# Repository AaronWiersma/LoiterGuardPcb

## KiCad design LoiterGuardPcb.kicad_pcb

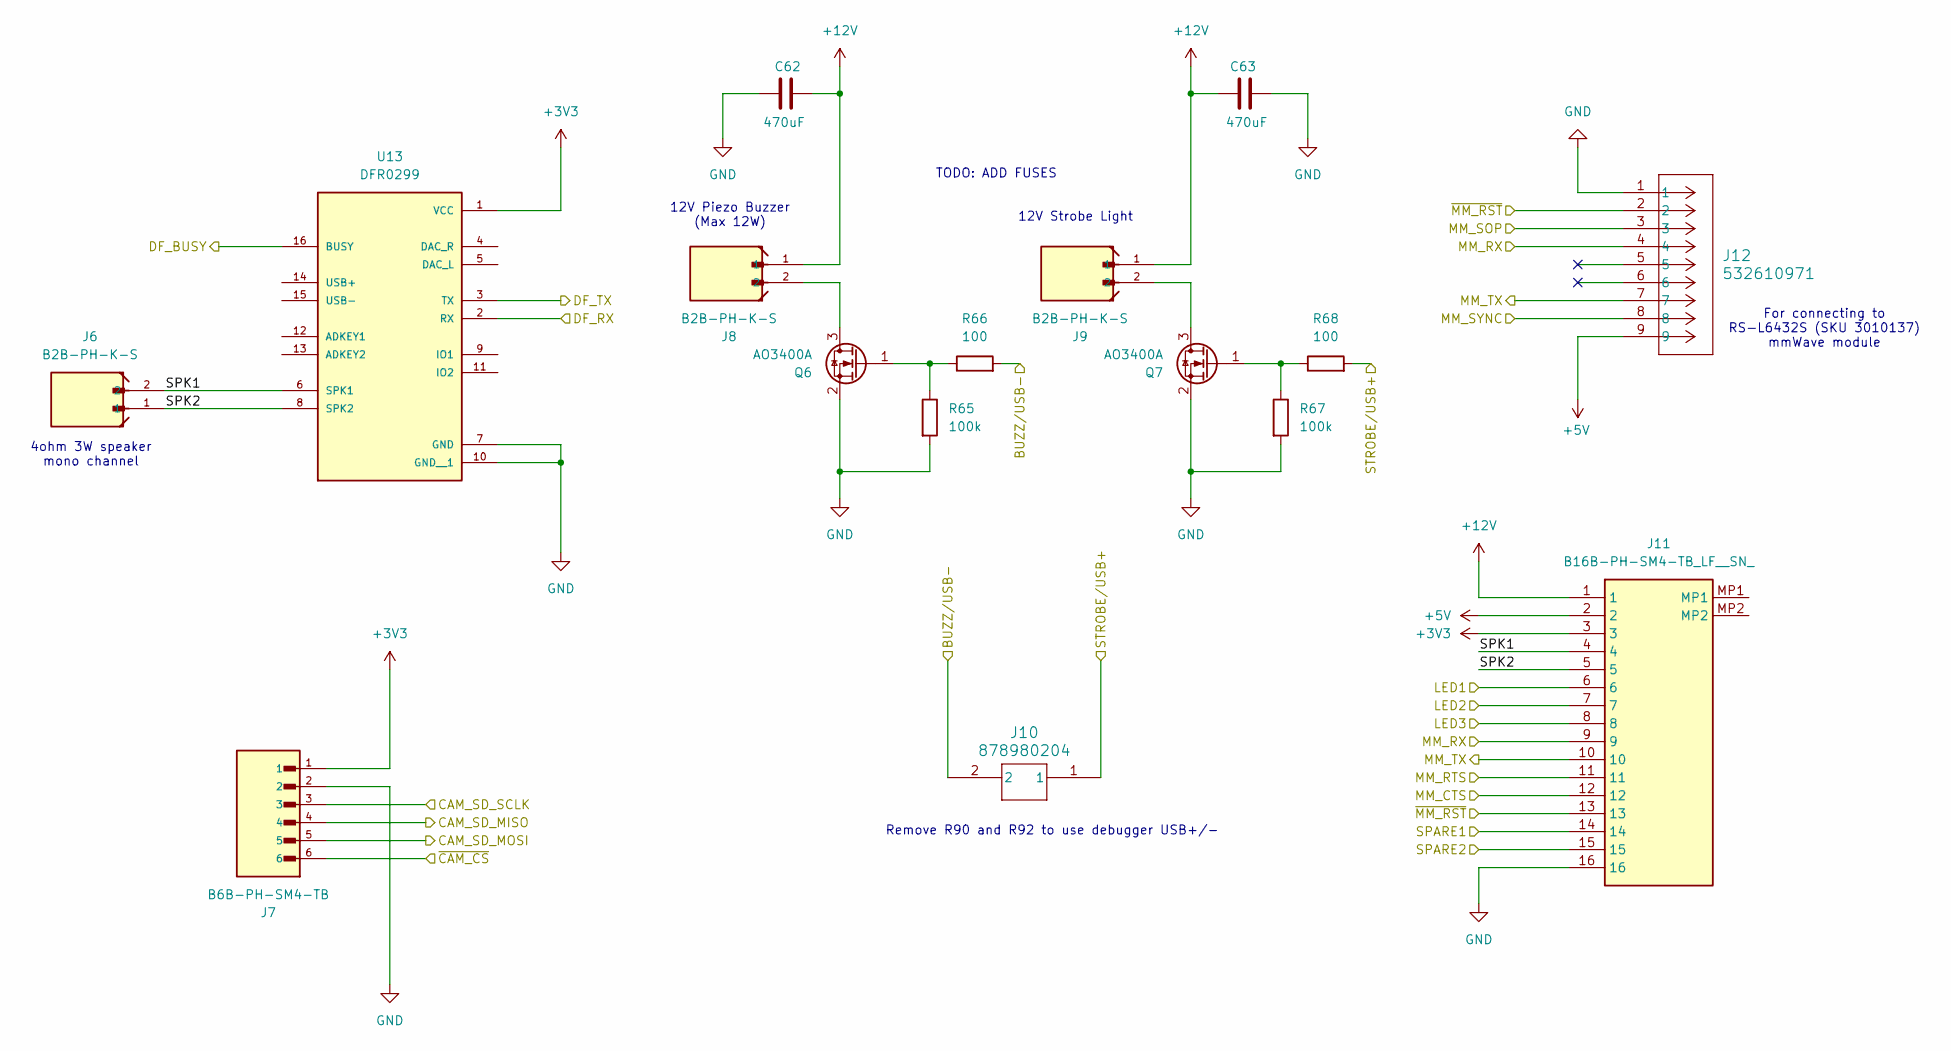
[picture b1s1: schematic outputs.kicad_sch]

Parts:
C62, C63: 470uF; CP_Radial_D10.0mm_P5.00mm
J6, J8, J9: B2B-PH-K-S; JST_B2B-PH-K-S
J7: B6B-PH-SM4-TB; JST_B6B-PH-SM4-TB; PARTREV N/A
J10: 878980204; 87898-0204_MOL
J11: B16B-PH-SM4-TB_LF__SN_; B16BPHSM4TBLFSN; Manufacturer_Part_Number B16B-PH-SM4-TB(LF)(SN); Mouser Part Number 306-B16BPHSM4TBLFSN
J12: 532610971; CONN_532610001-SD_09_MOL
Q6, Q7: AO3400A; SOT-23
R65, R67: 100k; R_0603_1608Metric
R66, R68: 100; R_0603_1608Metric
U13: DFR0299; MODULE_DFR0299

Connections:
+3V3: J7.1, J11.3, U13.1 (VCC); also elsewhere on the board
+5V: J11.2, J12.9; also elsewhere on the board
+12V: C62.2, C63.2, J8.1, J9.1, J11.1; also elsewhere on the board
/Expander/CAM_SD_MISO: J7.4; also elsewhere on the board
/Expander/CAM_SD_MOSI: J7.5; also elsewhere on the board
/Expander/CAM_SD_SCLK: J7.3; also elsewhere on the board
/Expander/DF_BUSY: U13.16 (BUSY); also elsewhere on the board
/Expander/MM_SOP: J12.3; also elsewhere on the board
/Expander/MM_SYNC: J12.8; also elsewhere on the board
/Expander/SPARE1: J11.15; also elsewhere on the board
/Expander/SPARE2: J11.14; also elsewhere on the board
/Expander/~MM_RST: J11.13, J12.2; also elsewhere on the board
/MCU/BUZZ/USB-: J10.2, R66.2; also elsewhere on the board
/MCU/DF_RX: U13.2 (RX); also elsewhere on the board
/MCU/DF_TX: U13.3 (TX); also elsewhere on the board
/MCU/LED1: J11.6; also elsewhere on the board
/MCU/LED2: J11.7; also elsewhere on the board
/MCU/LED3: J11.8; also elsewhere on the board
/MCU/MM_CTS: J11.12; also elsewhere on the board
/MCU/MM_RTS: J11.11; also elsewhere on the board
/MCU/MM_RX: J11.9, J12.4; also elsewhere on the board
/MCU/MM_TX: J11.10, J12.7; also elsewhere on the board
/MCU/STROBE/USB+: J10.1, R68.2; also elsewhere on the board
/MCU/~CAM_CS: J7.6; also elsewhere on the board
/Outputs/SPK1: J6.2, J11.4, U13.6 (SPK1)
/Outputs/SPK2: J6.1, J11.5, U13.8 (SPK2)
GND: C62.1, C63.1, J7.2, J11.16, J12.1, Q6.2 (S), Q7.2 (S), R65.2, R67.2, U13.7 (GND), U13.10 (GND__1); also elsewhere on the board
unnamed: J8.2, Q6.3 (D)
unnamed: Q6.1 (G), R65.1, R66.1
unnamed: J9.2, Q7.3 (D)
unnamed: Q7.1 (G), R67.1, R68.1

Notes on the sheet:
TODO: ADD FUSES
12V Strobe Light
Remove R90 and R92 to use debugger USB+/-
12V Piezo Buzzer (Max 12W)
4ohm 3W speaker mono channel
For connecting to RS-L6432S (SKU 3010137) mmWave module

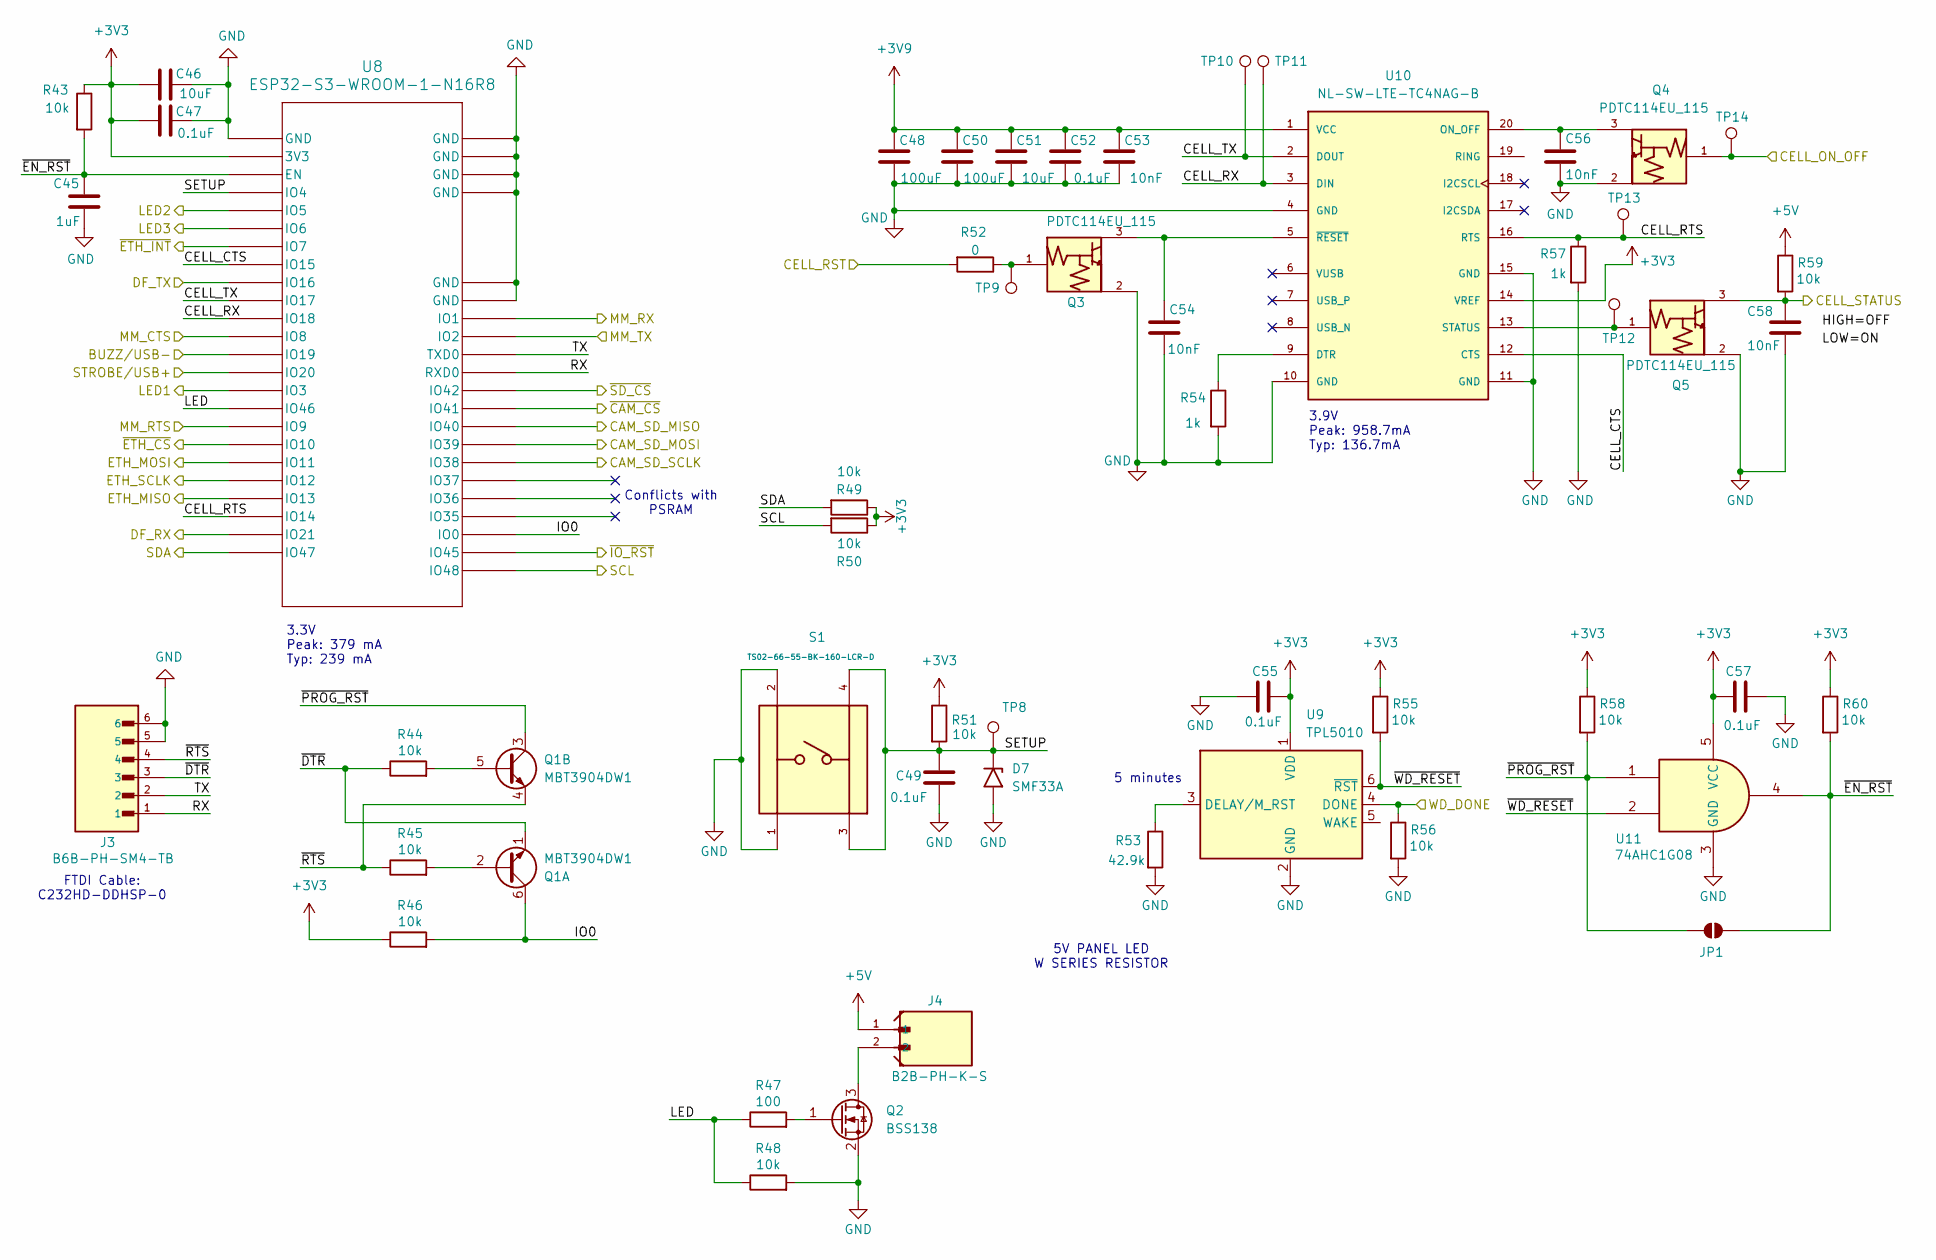
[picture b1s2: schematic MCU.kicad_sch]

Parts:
C45: 1uF; C_0603_1608Metric
C46, C51: 10uF; C_0805_2012Metric
C47, C49, C52, C55, C57: 0.1uF; C_0603_1608Metric
C48, C50: 100uF; CAPMP7.6X4.3_4.3N_KEM
C53, C54, C56, C58: 10nF; C_0603_1608Metric
D7: SMF33A; D_SMF
J3: B6B-PH-SM4-TB; JST_B6B-PH-SM4-TB; PARTREV N/A
J4: B2B-PH-K-S; JST_B2B-PH-K-S
JP1: SolderJumper_2_Open; SolderJumper-2_P1.3mm_Open_Pad1.0x1.5mm
Q1: MBT3904DW1; SOT-363_SC-70-6
Q2: BSS138; SOT-23
Q3, Q4, Q5: PDTC114EU_115; SOT65P210X110-3N; PARTREV 12
R43, R44, R45, R46, R48, R51, R55, R56, R58, R59, R60: 10k; R_0603_1608Metric
R47: 100; R_0603_1608Metric
R49, R50: 10k_0402_0402WGF1002TCE; R_0402_1005Metric; Tolerance 1%; MPN 0402WGF1002TCE
R52: 0; R_0603_1608Metric
R53: 42.9k; R_0603_1608Metric
R54, R57: 1k; R_0603_1608Metric
S1: TS02-66-55-BK-160-LCR-D; SW_TS02-66-55-BK-160-LCR-D; PARTREV 1.0
TP8, TP9, TP10, TP11, TP12, TP13, TP14: TestPoint; TestPoint_Pad_D2.0mm
U8: ESP32-S3-WROOM-1-N16R8; ESP32-S3-WROOM-1_EXP
U9: TPL5010; SOT-23-6
U10: NL-SW-LTE-TC4NAG-B; MODULE_NL-SW-LTE-QBG96; PARTREV 16
U11: 74AHC1G08; SOT95P280X140-5N

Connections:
+3V3: C46.1, C47.1, C55.2, C57.1, R43.1, R46.1, R49.1, R50.1, R51.1, R55.1, R58.1, R60.1, U8.2 (3V3), U9.1 (VDD), U10.14 (VREF), U11.5 (VCC); also elsewhere on the board
+3V9: C48.1, C50.1, C51.1, C52.1, C53.1, U10.1 (VCC); also elsewhere on the board
+5V: J4.1, R59.1; also elsewhere on the board
/Expander/CAM_SD_MISO: U8.33 (IO40); also elsewhere on the board
/Expander/CAM_SD_MOSI: U8.32 (IO39); also elsewhere on the board
/Expander/CAM_SD_SCLK: U8.31 (IO38); also elsewhere on the board
/Expander/CELL_ON_OFF: Q4.1, TP14.1; also elsewhere on the board
/Expander/CELL_RST: R52.2; also elsewhere on the board
/Expander/CELL_STATUS: C58.1, Q5.3, R59.2; also elsewhere on the board
/Expander/WD_DONE: R56.1, U9.4 (DONE); also elsewhere on the board
/Expander/~IO_RST: U8.26 (IO45); also elsewhere on the board
/Expander/~SD_CS: U8.35 (IO42); also elsewhere on the board
/MCU/BUZZ/USB-: U8.13 (IO19); also elsewhere on the board
/MCU/CELL_CTS: U8.8 (IO15), U10.12 (CTS)
/MCU/CELL_RTS: R57.1, TP13.1, U8.22 (IO14), U10.16 (RTS)
/MCU/CELL_RX: TP11.1, U8.11 (IO18), U10.3 (DIN)
/MCU/CELL_TX: TP10.1, U8.10 (IO17), U10.2 (DOUT)
/MCU/DF_RX: U8.23 (IO21); also elsewhere on the board
/MCU/DF_TX: U8.9 (IO16); also elsewhere on the board
/MCU/ETH_MISO: U8.21 (IO13); also elsewhere on the board
/MCU/ETH_MOSI: U8.19 (IO11); also elsewhere on the board
/MCU/ETH_SCLK: U8.20 (IO12); also elsewhere on the board
/MCU/IO0: Q1.6 (C1), R46.2, U8.27 (IO0)
/MCU/LED: R47.1, R48.1, U8.16 (IO46)
/MCU/LED1: U8.15 (IO3); also elsewhere on the board
/MCU/LED2: U8.5 (IO5); also elsewhere on the board
/MCU/LED3: U8.6 (IO6); also elsewhere on the board
/MCU/MM_CTS: U8.12 (IO8); also elsewhere on the board
/MCU/MM_RTS: U8.17 (IO9); also elsewhere on the board
/MCU/MM_RX: U8.39 (IO1); also elsewhere on the board
/MCU/MM_TX: U8.38 (IO2); also elsewhere on the board
/MCU/RX: J3.1, U8.36 (RXD0)
/MCU/SCL: R50.2, U8.25 (IO48); also elsewhere on the board
/MCU/SDA: R49.2, U8.24 (IO47); also elsewhere on the board
/MCU/SETUP: C49.1, D7.1 (A1), R51.2, S1.3, S1.4, TP8.1, U8.4 (IO4)
/MCU/STROBE/USB+: U8.14 (IO20); also elsewhere on the board
/MCU/TX: J3.2, U8.37 (TXD0)
/MCU/~CAM_CS: U8.34 (IO41); also elsewhere on the board
/MCU/~DTR: J3.3, Q1.1 (E1), R44.1
/MCU/~EN_RST: C45.2, JP1.2 (B), R43.2, R60.2, U8.3 (EN), U11.4
/MCU/~ETH_CS: U8.18 (IO10); also elsewhere on the board
/MCU/~ETH_INT: U8.7 (IO7); also elsewhere on the board
/MCU/~PROG_RST: JP1.1 (A), Q1.3 (C2), R58.2, U11.1
/MCU/~RTS: J3.4, Q1.4 (E2), R45.1
/MCU/~WD_RESET: R55.2, U9.6 (~RST), U11.2
GND: C45.1, C46.2, C47.2, C48.2, C49.2, C50.2, C51.2, C52.2, C53.2, C54.2, C55.1, C56.2, C57.2, C58.2, D7.2 (A2), J3.5, J3.6, Q2.2 (S), Q3.2, Q4.2, Q5.2, R48.2, R53.2, R54.2, R56.2, R57.2, S1.1, S1.2, U8.1 (GND), U8.40 (GND), U8.41 (GND), U8.46 (GND), U8.47 (GND), U8.48 (GND), U8.49 (GND), U9.2 (GND), U10.4 (GND), U10.10 (GND), U10.11 (GND), U10.15 (GND), U11.3 (GND); also elsewhere on the board
unnamed: Q1.2 (B1), R45.2
unnamed: Q1.5 (B2), R44.2
unnamed: J4.2, Q2.3 (D)
unnamed: Q2.1 (G), R47.2
unnamed: Q3.1, R52.1, TP9.1
unnamed: R53.1, U9.3 (DELAY/M_RST)
unnamed: R54.1, U10.9 (DTR)
unnamed: C56.1, Q4.3, U10.20 (ON_OFF)
unnamed: Q5.1, TP12.1, U10.13 (STATUS)
unnamed: C54.1, Q3.3, U10.5 (~RESET)

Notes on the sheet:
3.3V Peak: 379 mA Typ: 239 mA
3.9V Peak: 958.7mA Typ: 136.7mA
5V PANEL LED W SERIES RESISTOR
FTDI Cable: C232HD-DDHSP-0
5 minutes
Conflicts with PSRAM

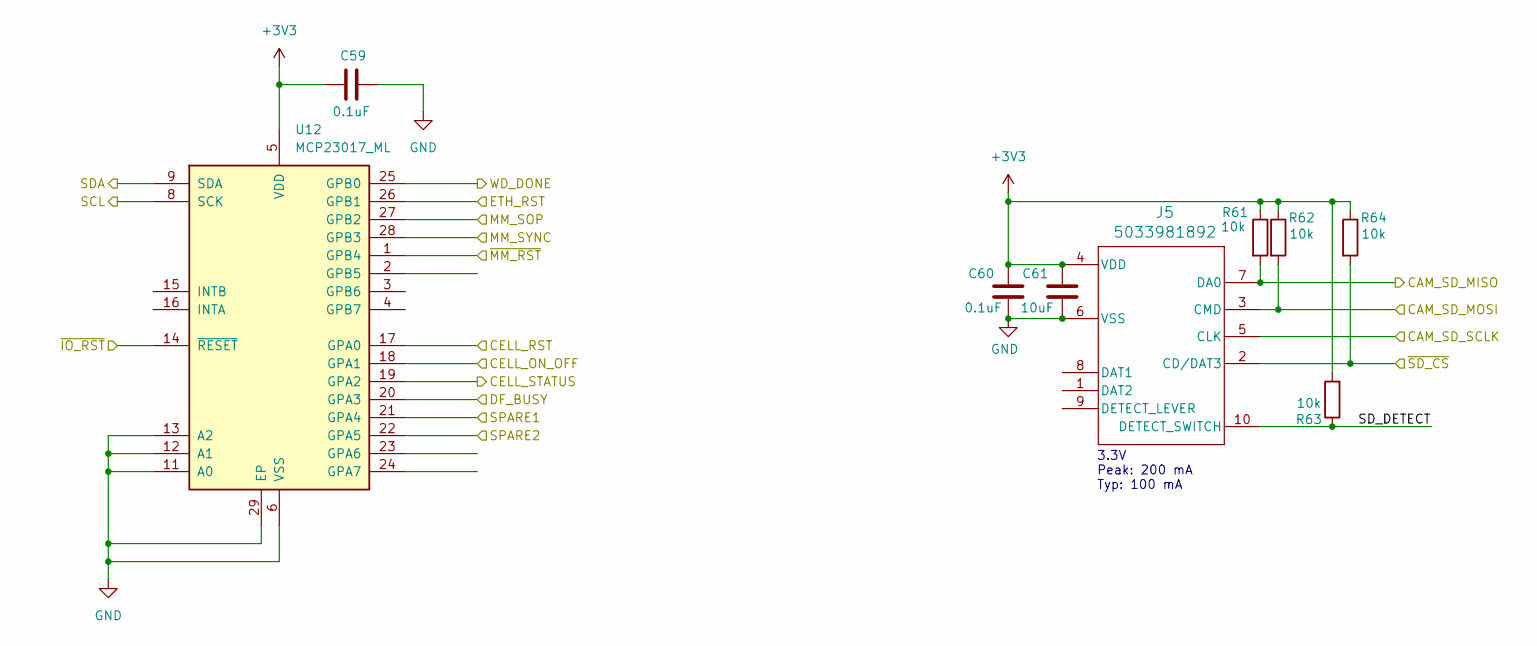
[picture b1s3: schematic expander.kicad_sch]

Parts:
C59, C60: 0.1uF; C_0603_1608Metric
C61: 10uF; C_0805_2012Metric
J5: 5033981892; CONN_503398-1892_MOL
R61, R62, R63, R64: 10k; R_0603_1608Metric
U12: MCP23017_ML; QFN-28-1EP_6x6mm_P0.65mm_EP4.25x4.25mm

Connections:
+3V3: C59.1, C60.1, C61.1, J5.4 (VDD), R61.1, R62.1, R63.2, R64.1, U12.5 (VDD); also elsewhere on the board
/Expander/CAM_SD_MISO: J5.7 (DA0), R61.2; also elsewhere on the board
/Expander/CAM_SD_MOSI: J5.3 (CMD), R62.2; also elsewhere on the board
/Expander/CAM_SD_SCLK: J5.5 (CLK); also elsewhere on the board
/Expander/CELL_ON_OFF: U12.18 (GPA1); also elsewhere on the board
/Expander/CELL_RST: U12.17 (GPA0); also elsewhere on the board
/Expander/CELL_STATUS: U12.19 (GPA2); also elsewhere on the board
/Expander/DF_BUSY: U12.20 (GPA3); also elsewhere on the board
/Expander/ETH_RST: U12.26 (GPB1); also elsewhere on the board
/Expander/MM_SOP: U12.27 (GPB2); also elsewhere on the board
/Expander/MM_SYNC: U12.28 (GPB3); also elsewhere on the board
/Expander/SD_DETECT: J5.10 (DETECT_SWITCH), R63.1
/Expander/SPARE1: U12.21 (GPA4); also elsewhere on the board
/Expander/SPARE2: U12.22 (GPA5); also elsewhere on the board
/Expander/WD_DONE: U12.25 (GPB0); also elsewhere on the board
/Expander/~IO_RST: U12.14 (~RESET); also elsewhere on the board
/Expander/~MM_RST: U12.1 (GPB4); also elsewhere on the board
/Expander/~SD_CS: J5.2 (CD/DAT3), R64.2; also elsewhere on the board
/MCU/SCL: U12.8 (SCK); also elsewhere on the board
/MCU/SDA: U12.9 (SDA); also elsewhere on the board
GND: C59.2, C60.2, C61.2, J5.6 (VSS), U12.6 (VSS), U12.11 (A0), U12.12 (A1), U12.13 (A2), U12.29 (EP); also elsewhere on the board

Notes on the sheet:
3.3V Peak: 200 mA Typ: 100 mA

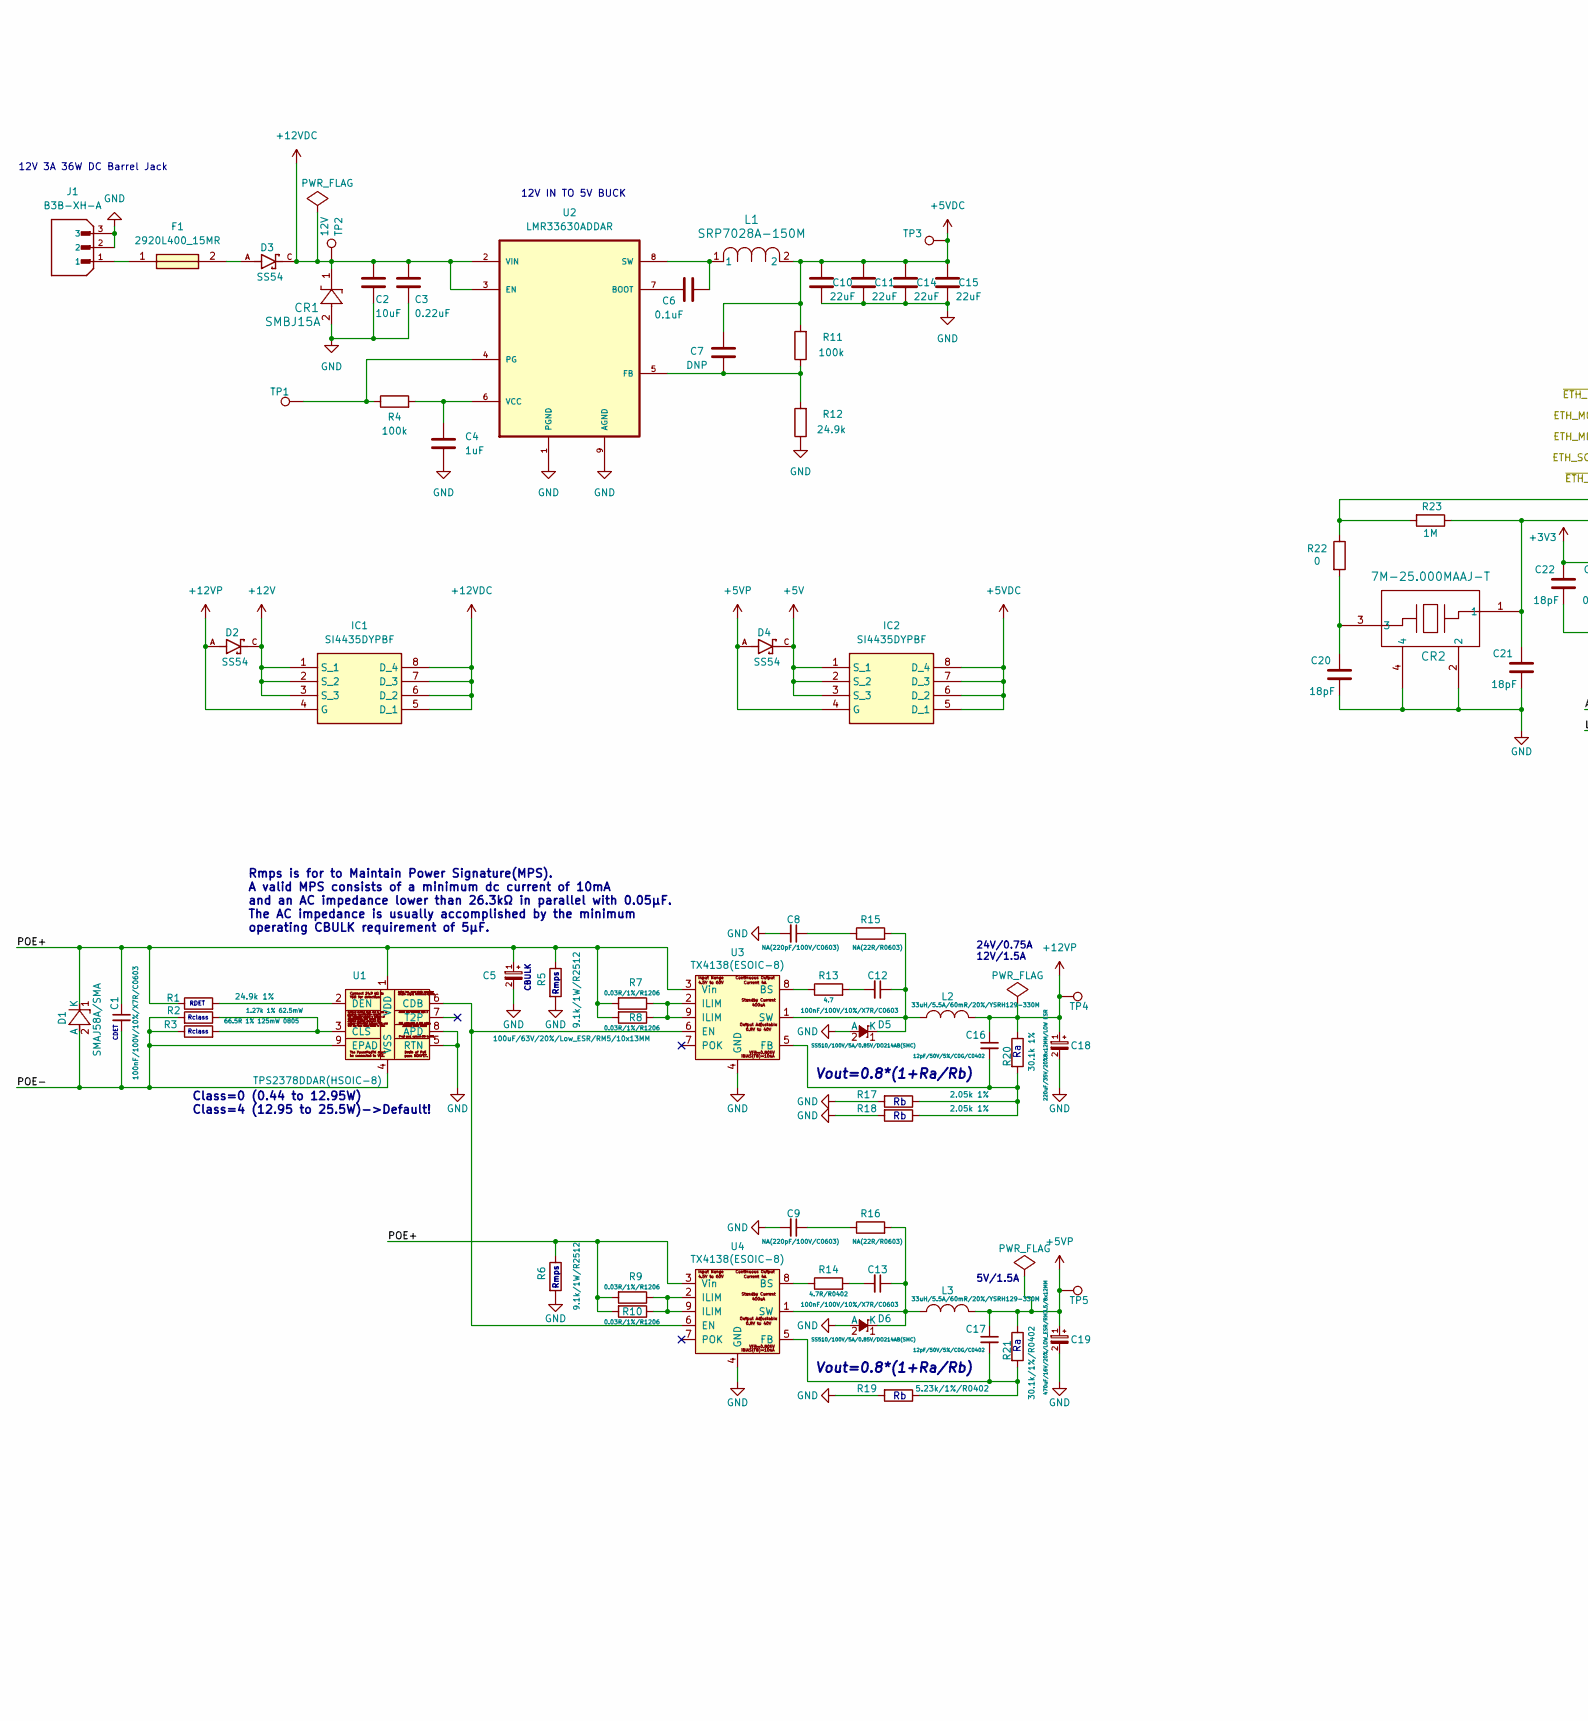
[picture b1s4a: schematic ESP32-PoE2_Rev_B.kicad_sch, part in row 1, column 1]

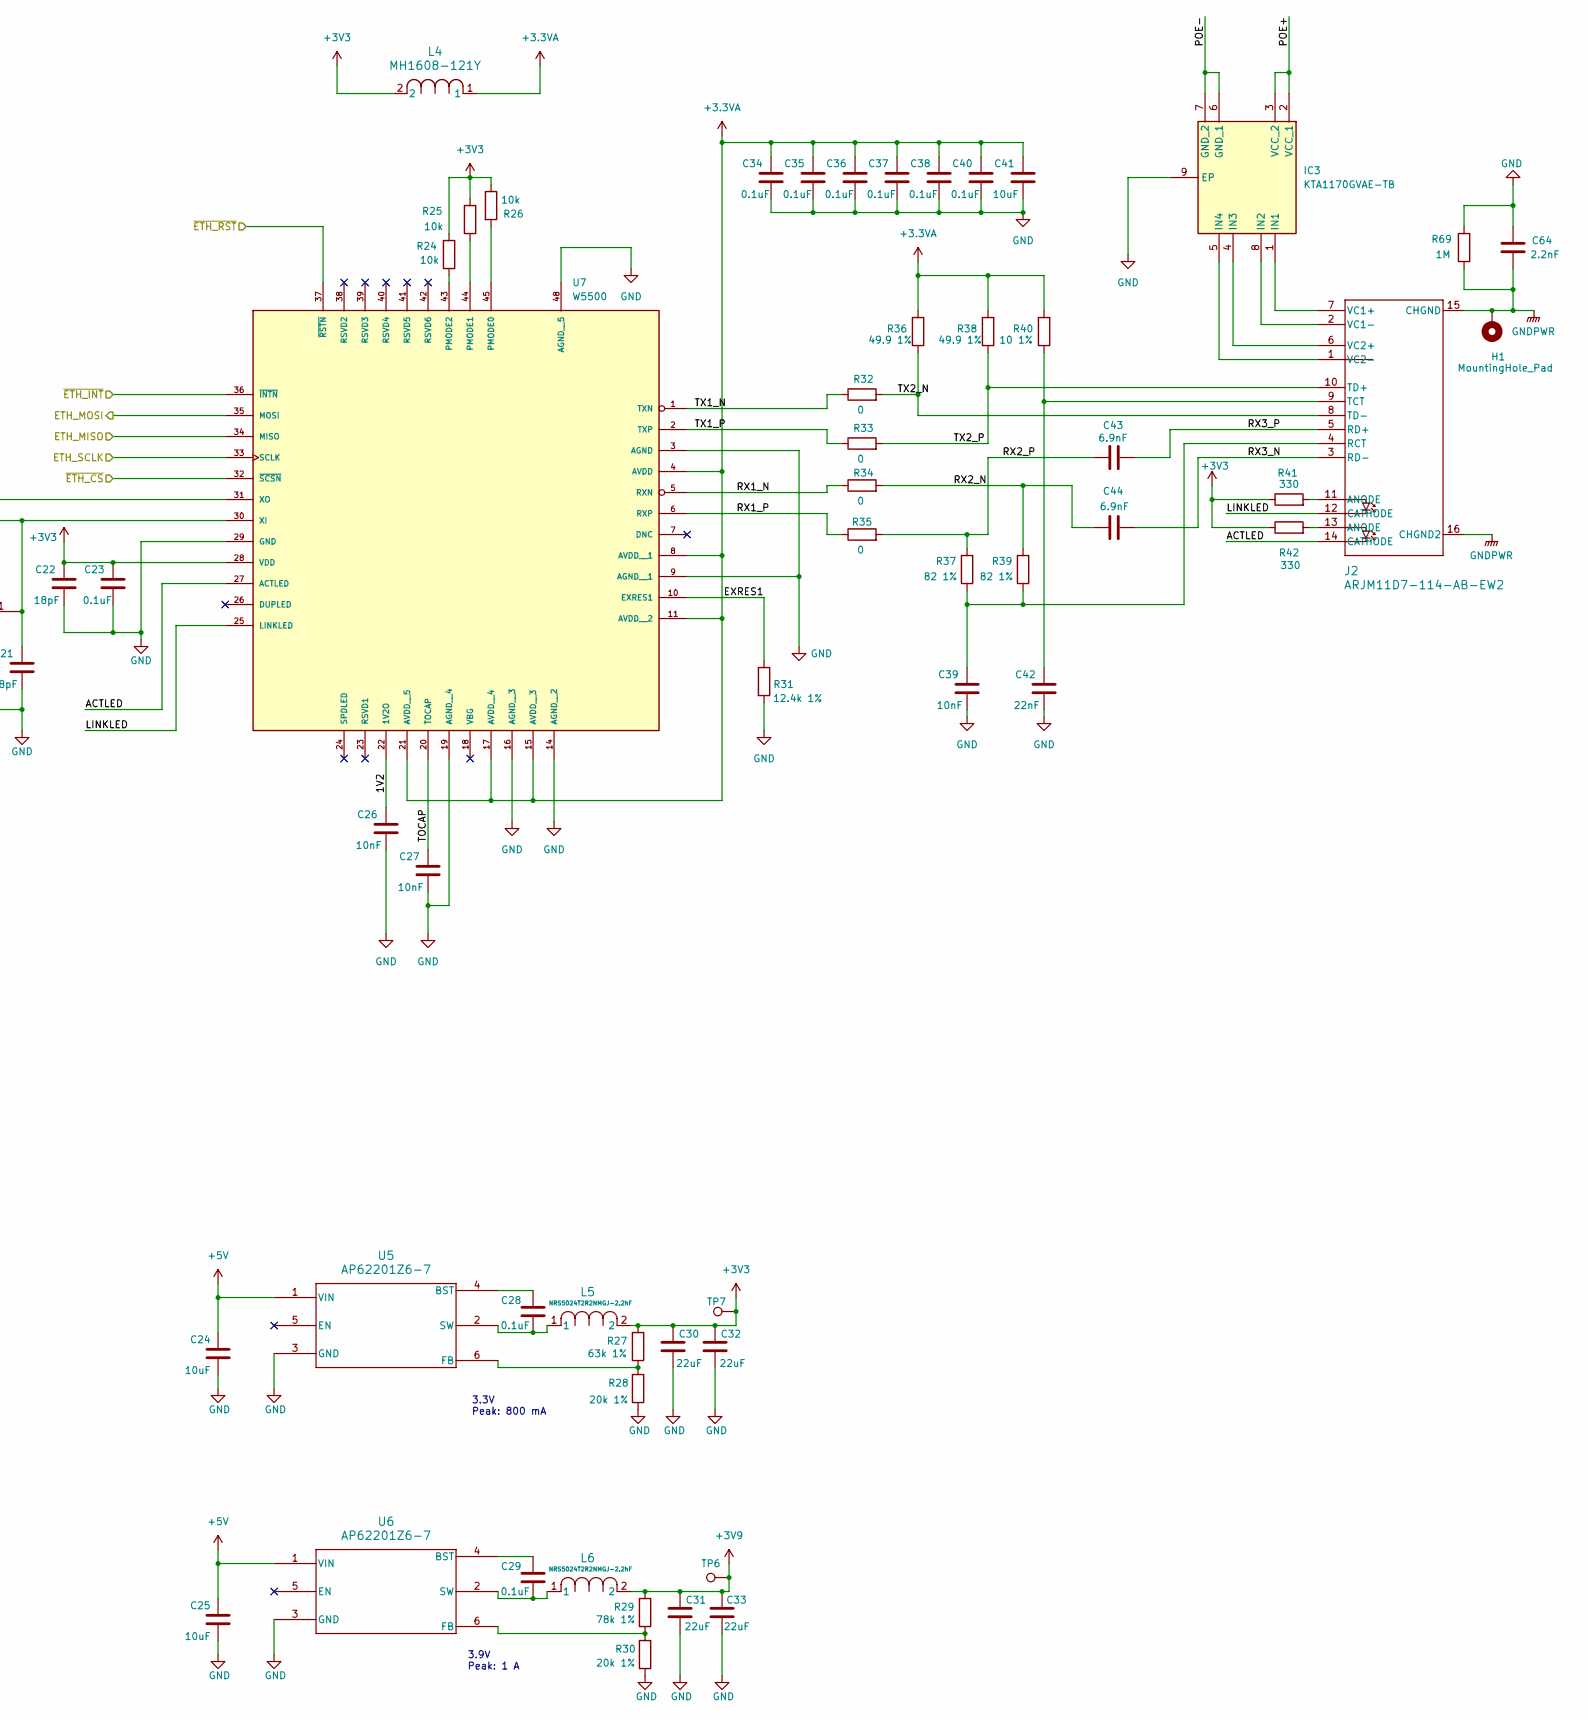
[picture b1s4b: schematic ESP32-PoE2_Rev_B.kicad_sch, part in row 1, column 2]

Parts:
C1: 100nF/100V/10%/X7R/C0603; C_0603_1608Metric
C2, C24, C25: 10uF; C_0805_2012Metric
C3: 0.22uF; C_0603_1608Metric
C4: 1uF; C_0603_1608Metric
C5: 100uF/63V/20%/Low_ESR/RM5/10x13MM; CPOL-RM5mm_10.0x16.0mm_PTH
C6, C23, C28, C29, C34, C35, C36, C37, C38, C40: 0.1uF; C_0603_1608Metric
C7: DNP; C_0603_1608Metric
C8, C9: NA(220pF/100V/C0603); C_0603_5MIL_DWS
C10, C11, C14, C15, C30, C31, C32, C33: 22uF; C_0805_2012Metric
C12, C13: 100nF/100V/10%/X7R/C0603; C_0603_5MIL_DWS
C16, C17: 12pF/50V/5%/C0G/C0402; C_0402_5MIL_DWS
C18: 220uF/35V/20%8x12MM/LOW ESR; CPOL-RM3.5mm_8.0x11.5mm_PTH
C19: 470uF/16V/20%/LOW_ESR/RM3.5/8x12MM; CPOL-RM3.5mm_8.0x11.5mm_PTH
C20, C21, C22: 18pF; C_0603_1608Metric
C26, C27, C39: 10nF; C_0603_1608Metric
C41: 10uF; C_0603_1608Metric
C42: 22nF; C_1206_3216Metric
C43, C44: 6.9nF; C_1206_3216Metric
C64: 2.2nF; C_1812_4532Metric
CR1: SMBJ15A; DO-214AASMB_J-BEND_LTF
CR2: 7M-25.000MAAJ-T; CRYSTAL_TXC_7M
D1: SMAJ58A/SMA; SMA-KA
D2, D3, D4: SS54; DIOM7959X265N; PARTREV 31 Aug 2016
D5, D6: SS510/100V/5A/0.85V/DO214AB(SMC); DO214AB(SMC)_1(K)-2(A)
F1: 2920L400_15MR; 2920L07560MR; Manufacturer_Part_Number 2920L400/15MR; Mouser Part Number 576-2920L400/15MR
H1: MountingHole_Pad; MountingHole_3mm_Pad_TopOnly
IC1, IC2: SI4435DYPBF; SOIC127P600X175-8N; Manufacturer_Part_Number SI4435DYPBF; Mouser Part Number 942-SI4435DYPBF
IC3: KTA1170GVAE-TB; SON65P400X400X80-9N; Manufacturer_Part_Number KTA1170GVAE-TB; Mouser Part Number 389-KTA1170GVAE-TB
J1: B3B-XH-A; JST_B3B-XH-A; PARTREV 7/4/21
J2: ARJM11D7-114-AB-EW2; CONN_ARJM11D7-114-AB-EW2_ABR
L1: SRP7028A-150M; IND_SRP7028A_BRN
L2, L3: 33uH/5.5A/60mR/20%/YSRH129-330M; HSMRH129_12.0x12.5x9.5(max)
L4: MH1608-121Y; IND_BOURNS_MH1608
L5, L6: NRS5024T2R2NMGJ-2.2hF; IND_NRS5024_TAY
R1: 24.9k 1%; R_0402_5MIL_DWS
R2: 1.27k 1% 62.5mW; R_0402_5MIL_DWS
R3: 66.5R 1% 125mW 0805; R_0805_5MIL_DWS
R4, R11: 100k; R_0603_1608Metric
R5, R6: 9.1k/1W/R2512; R_2512_MM_DWS
R7, R8, R9, R10: 0.03R/1%/R1206; R_1206_5MIL_DWS
R12: 24.9k; R_0603_1608Metric
R13: 4.7; R_0402_5MIL_DWS
R14: 4.7R/R0402; R_0402_5MIL_DWS
R15, R16: NA(22R/R0603); R_0603_5MIL_DWS
R17, R18: 2.05k 1%; R_0402_5MIL_DWS
R19: 5.23k/1%/R0402; R_0402_5MIL_DWS
R20: 30.1k 1%; R_0402_5MIL_DWS
R21: 30.1k/1%/R0402; R_0402_5MIL_DWS
R22, R32, R33, R34, R35: 0; R_0603_1608Metric
R23: 1M; R_0603_1608Metric
R24, R25, R26: 10k; R_0603_1608Metric
R27: 63k 1%; R_0603_1608Metric
R28, R30: 20k 1%; R_0603_1608Metric
R29: 78k 1%; R_0603_1608Metric
R31: 12.4k 1%; R_0603_1608Metric
R36, R38: 49.9 1%; R_0603_1608Metric
R37, R39: 82 1%; R_0603_1608Metric
R40: 10 1%; R_0603_1608Metric
R41, R42: 330; R_0603_1608Metric
R69: 1M; R_1206_3216Metric
TP1: TestPoint; TestPoint_Pad_D2.0mm
TP2: 12V; TestPoint_Pad_D2.0mm
TP3: 5VIN; TestPoint_Pad_D2.0mm
TP4, TP5, TP7: 3V3; TestPoint_Pad_D2.0mm
TP6: 3V9; TestPoint_Pad_D2.0mm
U1: TPS2378DDAR(HSOIC-8); ESOIC-8
U2: LMR33630ADDAR; VREG_LM5017MR_NOPB
U3, U4: TX4138(ESOIC-8); ESOIC-8
U5, U6: AP62201Z6-7; SOT563-Z6_1_DIO
U7: W5500; QFP50P900X900X160-48N

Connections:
+3.3VA: C34.1, C35.1, C36.1, C37.1, C38.1, C40.1, C41.1, L4.1, R36.2, R38.2, R40.2, U7.4 (AVDD), U7.8 (AVDD__1), U7.11 (AVDD__2), U7.15 (AVDD__3), U7.17 (AVDD__4), U7.21 (AVDD__5)
+3V3: C22.1, C23.1, C30.2, C32.2, L4.2, L5.2, R24.2, R25.2, R26.1, R27.2, R41.1, R42.1, TP7.1, U7.28 (VDD); also elsewhere on the board
+3V9: C31.2, C33.2, L6.2, R29.2, TP6.1; also elsewhere on the board
+5V: C24.2, C25.2, D4.C, IC2.1 (S_1), IC2.2 (S_2), IC2.3 (S_3), U5.1 (VIN), U6.1 (VIN); also elsewhere on the board
+5VDC: C7.1, C10.1, C11.1, C14.1, C15.1, IC2.5 (D_1), IC2.6 (D_2), IC2.7 (D_3), IC2.8 (D_4), L1.2, R11.2, TP3.1
+5VP: C17.1, C19.1 (+), D4.A, IC2.4 (G), L3.2, R21.1, TP5.1
+12V: D2.C, IC1.1 (S_1), IC1.2 (S_2), IC1.3 (S_3); also elsewhere on the board
+12VDC: C2.1, C3.1, CR1.1, D3.C, IC1.5 (D_1), IC1.6 (D_2), IC1.7 (D_3), IC1.8 (D_4), TP2.1, U2.2 (VIN), U2.3 (EN)
+12VP: C16.1, C18.1 (+), D2.A, IC1.4 (G), L2.2, R20.1, TP4.1
/Expander/ETH_RST: U7.37 (~RSTN); also elsewhere on the board
/MCU/ETH_MISO: U7.35 (MOSI); also elsewhere on the board
/MCU/ETH_MOSI: U7.34 (MISO); also elsewhere on the board
/MCU/ETH_SCLK: U7.33 (SCLK); also elsewhere on the board
/MCU/~ETH_CS: U7.32 (~SCSN); also elsewhere on the board
/MCU/~ETH_INT: U7.36 (~INTN); also elsewhere on the board
/Poe/1V2: C26.1, U7.22 (1V2O)
/Poe/ACTLED: J2.14 (CATHODE), U7.27 (ACTLED)
/Poe/EXRES1: R31.1, U7.10 (EXRES1)
/Poe/LINKLED: J2.12 (CATHODE), U7.25 (LINKLED)
/Poe/POE+: C1.1, C5.1 (+), D1.1 (K), IC3.2 (VCC_1), IC3.3 (VCC_2), R1.1, R5.1, R6.1, R7.2, R8.2, R9.2, R10.2, U1.1 (VDD), U3.3 (Vin), U4.3 (Vin)
/Poe/POE-: C1.2, D1.2 (A), IC3.6 (GND_1), IC3.7 (GND_2), R2.2, R3.1, U1.4 (VSS), U1.9 (EPAD)
/Poe/RX1_N: R34.1, U7.5 (RXN)
/Poe/RX1_P: R35.1, U7.6 (RXP)
/Poe/RX2_N: C44.1, R34.2, R39.2
/Poe/RX2_P: C43.1, R35.2, R37.2
/Poe/RX3_N: C44.2, J2.3 (RD-)
/Poe/RX3_P: C43.2, J2.5 (RD+)
/Poe/TOCAP: C27.1, U7.20 (TOCAP)
/Poe/TX1_N: R32.1, U7.1 (TXN)
/Poe/TX1_P: R33.1, U7.2 (TXP)
/Poe/TX2_N: J2.8 (TD-), R32.2, R36.1
/Poe/TX2_P: J2.10 (TD+), R33.2, R38.1
GND: C2.2, C3.2, C4.2, C5.2 (-), C8.2, C9.2, C10.2, C11.2, C14.2, C15.2, C18.2 (-), C19.2 (-), C20.2, C21.2, C22.2, C23.2, C24.1, C25.1, C26.2, C27.2, C30.1, C31.1, C32.1, C33.1, C34.2, C35.2, C36.2, C37.2, C38.2, C39.2, C40.2, C41.2, C42.2, C64.1, CR1.2, CR2.2, CR2.4, D5.2 (A), D6.2 (A), IC3.9 (EP), J1.2, J1.3, R5.2, R6.2, R12.1, R17.2, R18.2, R19.2, R28.1, R30.1, R31.2, R69.2, U1.5 (RTN), U1.8 (APD), U2.1 (PGND), U2.9 (AGND), U3.4 (GND), U4.4 (GND), U5.3 (GND), U6.3 (GND), U7.3 (AGND), U7.9 (AGND__1), U7.14 (AGND__2), U7.16 (AGND__3), U7.19 (AGND__4), U7.29 (GND), U7.48 (AGND__5); also elsewhere on the board
GNDPWR: C64.2, H1.1, J2.15 (CHGND), J2.16 (CHGND2), R69.1
unnamed: C8.1, R15.1
unnamed: C9.1, R16.1
unnamed: C12.2, R13.2
unnamed: C13.2, R14.2
unnamed: C20.1, CR2.3, R22.2
unnamed: D3.A, F1.2
unnamed: C12.1, D5.1 (K), L2.1, R15.2, U3.1 (SW)
unnamed: C13.1, D6.1 (K), L3.1, R16.2, U4.1 (SW)
unnamed: F1.1, J1.1
unnamed: IC3.1 (IN1), J2.7 (VC1+)
unnamed: IC3.8 (IN2), J2.2 (VC1-)
unnamed: IC3.4 (IN3), J2.6 (VC2+)
unnamed: IC3.5 (IN4), J2.1 (VC2-)
unnamed: J2.11 (ANODE), R41.2
unnamed: J2.13 (ANODE), R42.2
unnamed: C39.1, J2.4 (RCT), R37.1, R39.1
unnamed: C42.1, J2.9 (TCT), R40.1
unnamed: R7.1, R8.1, U3.2 (ILIM), U3.9 (ILIM)
unnamed: R9.1, R10.1, U4.2 (ILIM), U4.9 (ILIM)
unnamed: U1.6 (CDB), U3.6 (EN), U4.6 (EN)
unnamed: R2.1, R3.2, U1.3 (CLS)
unnamed: R1.2, U1.2 (DEN)
unnamed: C6.2, U2.7 (BOOT)
unnamed: C7.2, R11.1, R12.2, U2.5 (FB)
unnamed: R4.1, TP1.1, U2.4 (PG)
unnamed: C6.1, L1.1, U2.8 (SW)
unnamed: C4.1, R4.2, U2.6 (VCC)
unnamed: R13.1, U3.8 (BS)
unnamed: C16.2, R17.1, R18.1, R20.2, U3.5 (FB)
unnamed: R14.1, U4.8 (BS)
unnamed: C17.2, R19.1, R21.2, U4.5 (FB)
unnamed: C28.2, U5.4 (BST)
unnamed: R27.1, R28.2, U5.6 (FB)
unnamed: C28.1, L5.1, U5.2 (SW)
unnamed: C29.2, U6.4 (BST)
unnamed: R29.1, R30.2, U6.6 (FB)
unnamed: C29.1, L6.1, U6.2 (SW)
unnamed: R26.2, U7.45 (PMODE0)
unnamed: R25.1, U7.44 (PMODE1)
unnamed: R24.1, U7.43 (PMODE2)
unnamed: C21.1, CR2.1, R23.1, U7.30 (XI)
unnamed: R22.1, R23.2, U7.31 (XO)

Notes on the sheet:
5V/1.5A
CDET
Rmps is for to Maintain Power Signature(MPS). A valid MPS consists of a minimum dc current of 10mA and an AC impedance lower than 26.3kΩ in parallel with 0.05μF. The AC impedance is usually accomplished by the minimum operating CBULK requirement of 5μF.
RDET
3.3V Peak: 800 mA
Rmps
Rclass
12V IN TO 5V BUCK
24V/0.75A 12V/1.5A
Vout=0.8*(1+Ra/Rb)
12V 3A 36W DC Barrel Jack
Class=0 (0.44 to 12.95W) Class=4 (12.95 to 25.5W)->Default!
3.9V Peak: 1 A
CBULK
